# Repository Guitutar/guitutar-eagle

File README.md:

# Guitutar PCB Layout - Eagle Files

This repository is used for version control of PCB layout files for the creation of the Guitutar guitar teaching device. 

All PCB layouts within this repository were created by the Guitutar development team: Austin Peterson, Brian Rieder, Cole Giannotti, Jen Isaza

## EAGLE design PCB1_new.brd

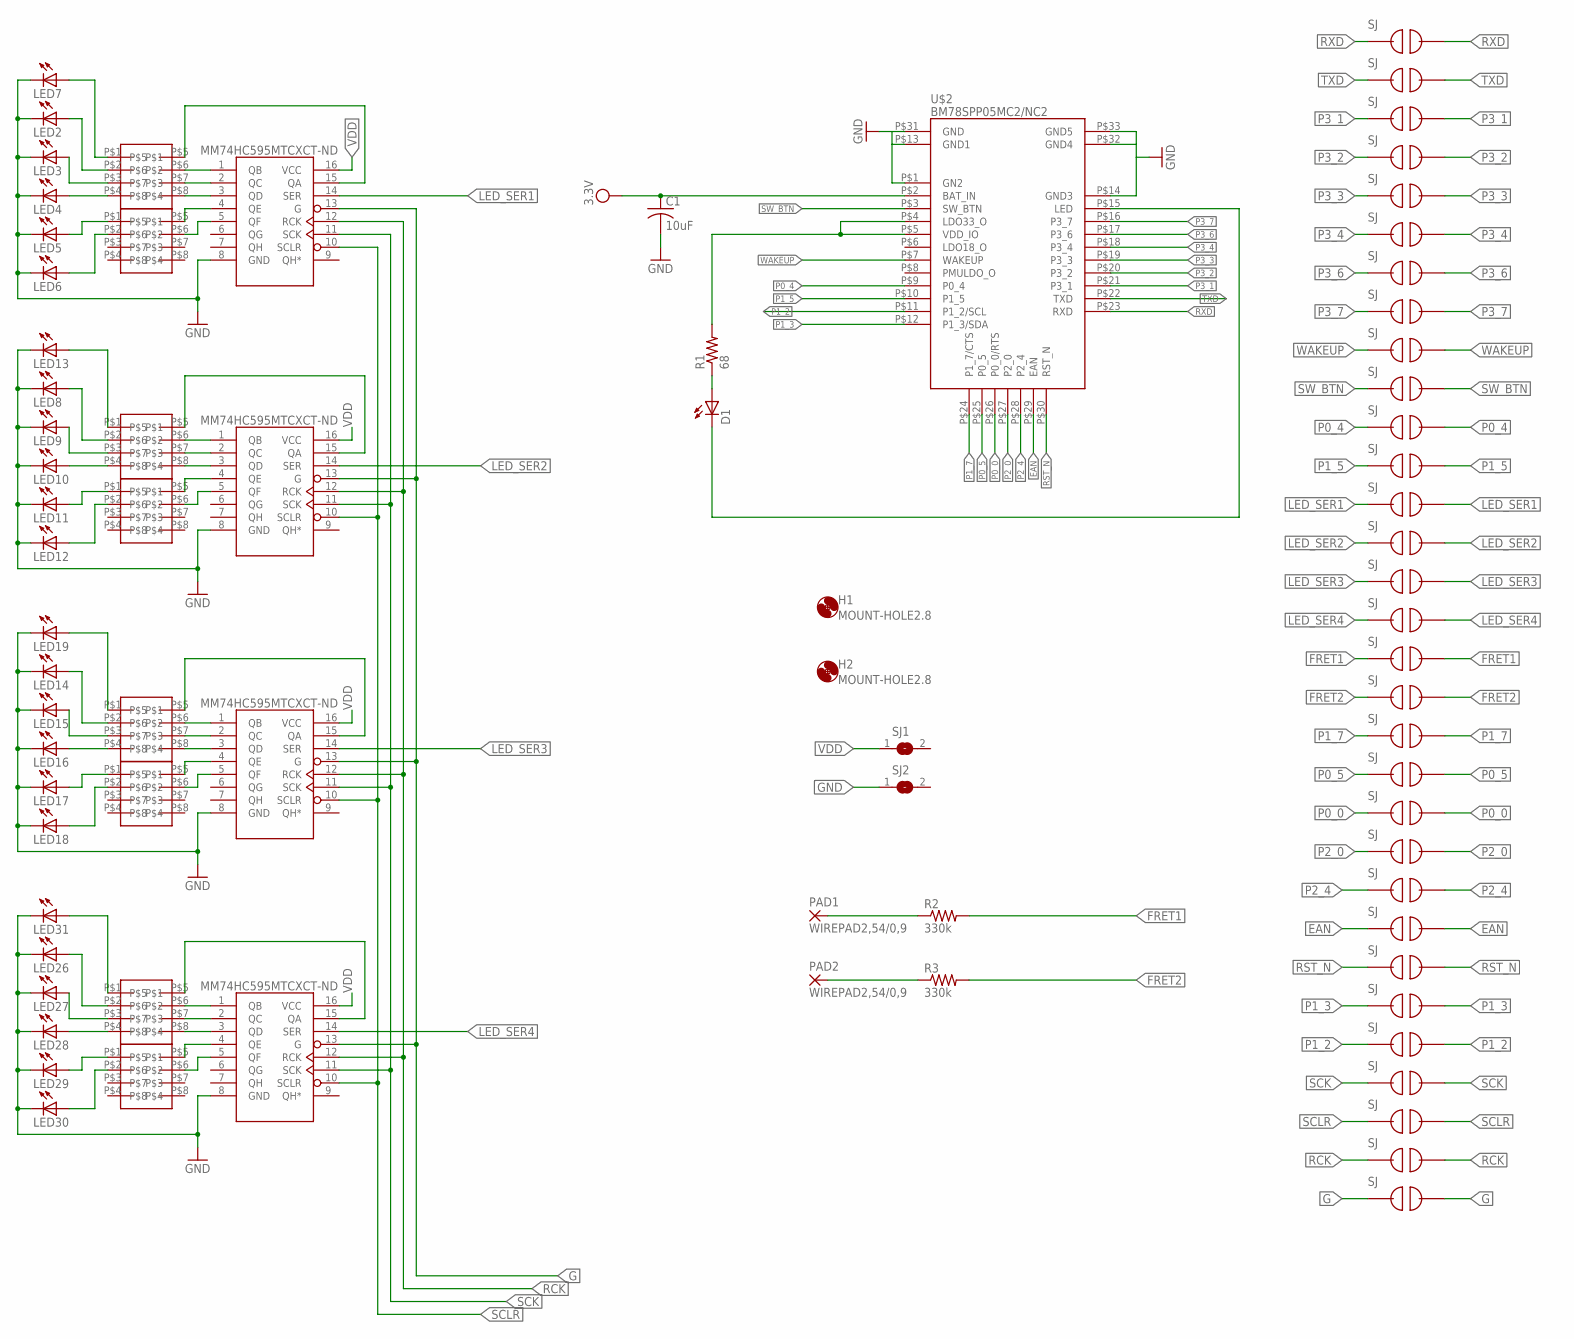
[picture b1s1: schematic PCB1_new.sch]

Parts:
C1: 10uF; C0805
D1: LEDSMT1206; 1206
H1, H2: MOUNT-HOLE2.8; 2,8
LED2, LED3, LED4, LED5, LED6, LED7, LED8, LED9, LED10, LED11, LED12, LED13, LED14, LED15, LED16, LED17, LED18, LED19, LED26, LED27, LED28, LED29, LED30, LED31: LEDSMT1206; 1206
PAD1, PAD2: WIREPAD2,54/0,9; 2,54/0,9
R1: 68; M0805
R2, R3: 330k; R0805
RN1, RN2: MNR04MRAPJ680; MNR04
SJ1, SJ2: SJW
U$1, U$3, U$4, U$5: MM74HC595TSSOP-LD16; MM74HC595MTCXCT-ND
U$2: BM78SPP05MC2/NC2
U$6, U$7, U$8, U$9, U$10, U$11, U$12, U$13, U$14, U$15, U$16, U$17, U$18, U$19, U$20, U$21, U$22, U$23, U$24, U$25, U$26, U$27, U$28, U$29, U$30, U$31, U$32, U$33, U$34, U$35, U$36: JUMPER
U$39, U$40, U$41, U$42, U$43, U$44: MNR04MRAPJ680; MNR04

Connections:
EAN: U$2.P$29 (EAN), U$26.P$1, U$26.P$2
FRET1: R2.2, U$19.P$1, U$19.P$2
FRET2: R3.2, U$20.P$1, U$20.P$2
G: U$1.13 (G), U$3.13 (G), U$4.13 (G), U$5.13 (G), U$30.P$1, U$30.P$2
GND: C1.2, LED2.C, LED3.C, LED4.C, LED5.C, LED6.C, LED7.C, LED8.C, LED9.C, LED10.C, LED11.C, LED12.C, LED13.C, LED14.C, LED15.C, LED16.C, LED17.C, LED18.C, LED19.C, LED26.C, LED27.C, LED28.C, LED29.C, LED30.C, LED31.C, SJ2.1, U$1.8 (GND), U$2.P$1 (GN2), U$2.P$13 (GND1), U$2.P$14 (GND3), U$2.P$31 (GND), U$2.P$32 (GND4), U$2.P$33 (GND5), U$3.8 (GND), U$4.8 (GND), U$5.8 (GND)
LED: D1.C, U$2.P$15 (LED)
LED_SER1: U$4.14 (SER), U$15.P$1, U$15.P$2
LED_SER2: U$1.14 (SER), U$16.P$1, U$16.P$2
LED_SER3: U$3.14 (SER), U$17.P$1, U$17.P$2
LED_SER4: U$5.14 (SER), U$18.P$1, U$18.P$2
unnamed: RN1.P$6, U$4.1 (QB)
unnamed: RN1.P$7, U$4.2 (QC)
unnamed: RN1.P$8, U$4.3 (QD)
unnamed: RN2.P$5, U$4.4 (QE)
unnamed: RN2.P$6, U$4.5 (QF)
unnamed: LED7.A, RN1.P$1
unnamed: RN1.P$5, U$4.15 (QA)
unnamed: LED2.A, RN1.P$2
unnamed: LED3.A, RN1.P$3
unnamed: LED4.A, RN1.P$4
unnamed: LED5.A, RN2.P$1
unnamed: LED6.A, RN2.P$2
unnamed: U$1.1 (QB), U$39.P$6
unnamed: U$1.2 (QC), U$39.P$7
unnamed: D1.A, R1.1
unnamed: R1.2, U$2.P$4 (LDO33_O), U$2.P$5 (VDD_IO)
unnamed: LED10.A, U$39.P$4
unnamed: LED16.A, U$41.P$4
unnamed: LED28.A, U$43.P$4
unnamed: U$1.3 (QD), U$39.P$8
unnamed: U$1.4 (QE), U$40.P$5
unnamed: U$1.5 (QF), U$40.P$6
unnamed: U$1.15 (QA), U$39.P$5
unnamed: LED13.A, U$39.P$1
unnamed: LED8.A, U$39.P$2
unnamed: LED9.A, U$39.P$3
unnamed: LED11.A, U$40.P$1
unnamed: LED12.A, U$40.P$2
unnamed: U$3.1 (QB), U$41.P$6
unnamed: U$3.2 (QC), U$41.P$7
unnamed: U$3.3 (QD), U$41.P$8
unnamed: U$3.4 (QE), U$42.P$5
unnamed: U$3.5 (QF), U$42.P$6
unnamed: U$3.15 (QA), U$41.P$5
unnamed: LED19.A, U$41.P$1
unnamed: LED14.A, U$41.P$2
unnamed: LED15.A, U$41.P$3
unnamed: LED17.A, U$42.P$1
unnamed: LED18.A, U$42.P$2
unnamed: U$5.1 (QB), U$43.P$6
unnamed: U$5.2 (QC), U$43.P$7
unnamed: U$5.3 (QD), U$43.P$8
unnamed: U$5.4 (QE), U$44.P$5
unnamed: U$5.5 (QF), U$44.P$6
unnamed: U$5.15 (QA), U$43.P$5
unnamed: LED31.A, U$43.P$1
unnamed: LED26.A, U$43.P$2
unnamed: LED27.A, U$43.P$3
unnamed: LED29.A, U$44.P$1
unnamed: LED30.A, U$44.P$2
unnamed: PAD1.1, R2.1
unnamed: PAD2.1, R3.1
P0_0: U$2.P$26 (P0_0/RTS), U$23.P$1, U$23.P$2
P0_4: U$2.P$9 (P0_4), U$13.P$1, U$13.P$2
P0_5: U$2.P$25 (P0_5), U$22.P$1, U$22.P$2
P1_2: U$2.P$11 (P1_2/SCL), U$29.P$1, U$29.P$2
P1_3: U$2.P$12 (P1_3/SDA), U$28.P$1, U$28.P$2
P1_5: U$2.P$10 (P1_5), U$14.P$1, U$14.P$2
P1_7: U$2.P$24 (P1_7/CTS), U$21.P$1, U$21.P$2
P2_0: U$2.P$27 (P2_0), U$24.P$1, U$24.P$2
P2_4: U$2.P$28 (P2_4), U$25.P$1, U$25.P$2
P3_1: U$2.P$21 (P3_1), U$33.P$1, U$33.P$2
P3_2: U$2.P$20 (P3_2), U$6.P$1, U$6.P$2
P3_3: U$2.P$19 (P3_3), U$7.P$1, U$7.P$2
P3_4: U$2.P$18 (P3_4), U$8.P$1, U$8.P$2
P3_6: U$2.P$17 (P3_6), U$9.P$1, U$9.P$2
P3_7: U$2.P$16 (P3_7), U$10.P$1, U$10.P$2
RCK: U$1.12 (RCK), U$3.12 (RCK), U$4.12 (RCK), U$5.12 (RCK), U$31.P$1, U$31.P$2
RST_N: U$2.P$30 (RST_N), U$27.P$1, U$27.P$2
RXD: U$2.P$23 (RXD), U$35.P$1, U$35.P$2
SCK: U$1.11 (SCK), U$3.11 (SCK), U$4.11 (SCK), U$5.11 (SCK), U$32.P$1, U$32.P$2
SCLR: U$1.10 (SCLR), U$3.10 (SCLR), U$4.10 (SCLR), U$5.10 (SCLR), U$36.P$1, U$36.P$2
SW_BTN: U$2.P$3 (SW_BTN), U$12.P$1, U$12.P$2
TXD: U$2.P$22 (TXD), U$34.P$1, U$34.P$2
VDD: C1.1, SJ1.1, U$1.16 (VCC), U$2.P$2 (BAT_IN), U$3.16 (VCC), U$4.16 (VCC), U$5.16 (VCC)
WAKEUP: U$2.P$7 (WAKEUP), U$11.P$1, U$11.P$2

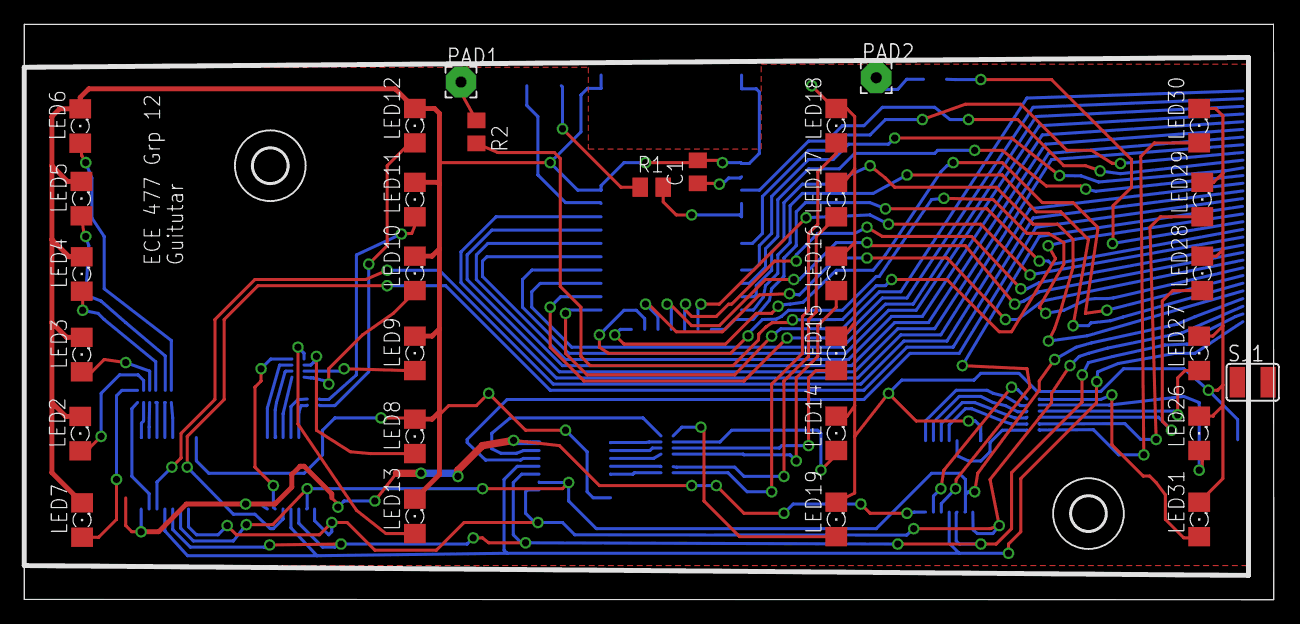
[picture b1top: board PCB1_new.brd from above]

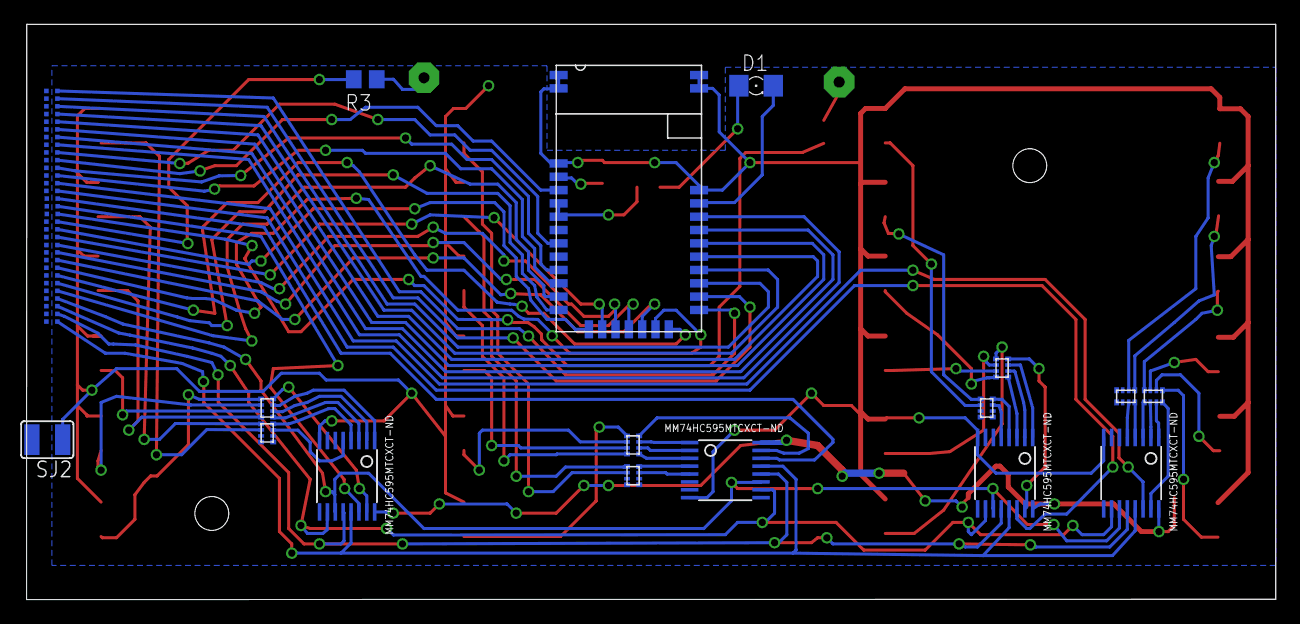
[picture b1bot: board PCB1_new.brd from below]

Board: 2 copper layers, 103.2 x 47.5 mm, 79 parts (47 on the bottom side), 86 nets.

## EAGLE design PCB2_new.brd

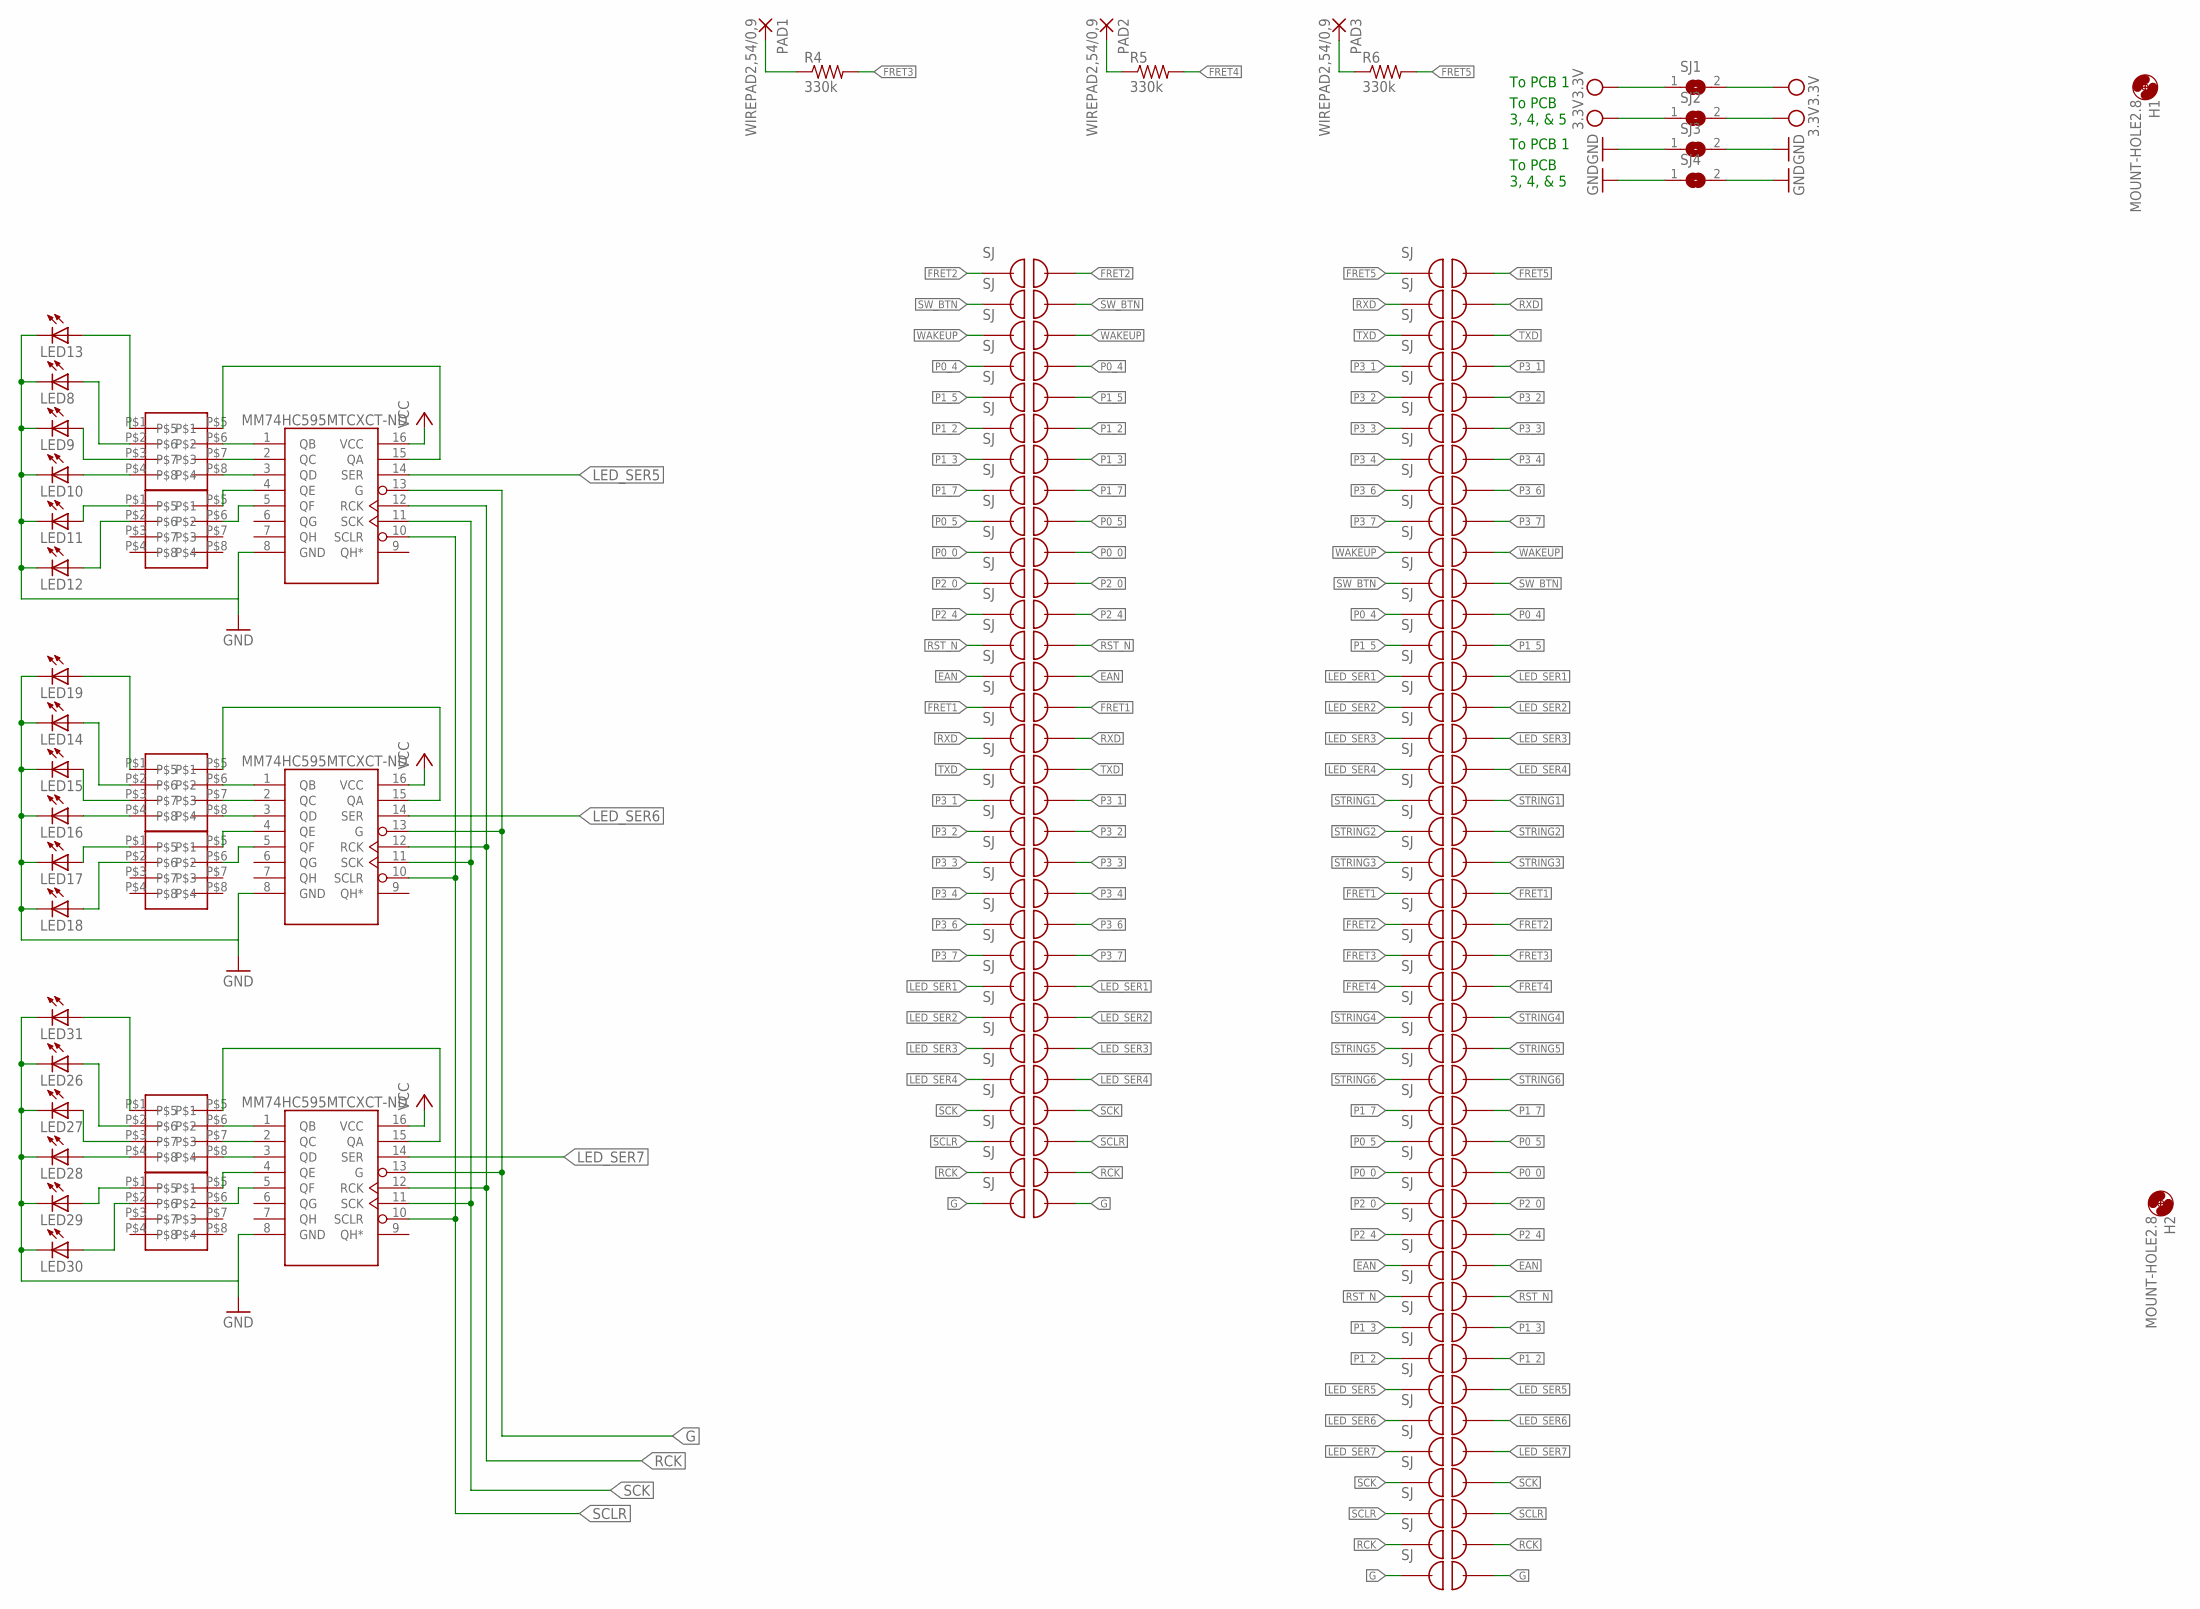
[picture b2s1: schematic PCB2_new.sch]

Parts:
H1, H2: MOUNT-HOLE2.8; 2,8
LED8, LED9, LED10, LED11, LED12, LED13, LED14, LED15, LED16, LED17, LED18, LED19, LED26, LED27, LED28, LED29, LED30, LED31: LEDSMT1206; 1206
PAD1, PAD2, PAD3: WIREPAD2,54/0,9; 2,54/0,9
R4, R5, R6: 330k; M0805
SJ1, SJ2, SJ3, SJ4: SJ
U$1, U$3, U$5: MM74HC595TSSOP-LD16; MM74HC595MTCXCT-ND
U$2, U$4, U$6, U$7, U$8, U$9, U$10, U$11, U$12, U$13, U$14, U$15, U$16, U$17, U$18, U$19, U$20, U$21, U$22, U$23, U$24, U$25, U$26, U$27, U$28, U$29, U$30, U$31, U$32, U$33, U$34, U$35, U$36, U$37, U$38, U$39, U$40, U$41, U$42, U$43, U$44, U$45, U$46, U$47, U$48, U$49, U$50, U$51, U$52, U$53, U$54, U$55, U$56, U$57, U$58, U$59, U$60, U$61, U$62, U$63, U$64, U$65, U$66, U$67, U$68, U$69, U$70, U$71, U$72, U$73, U$80, U$81, U$82, U$83: JUMPER
U$74, U$75, U$76, U$77, U$78, U$79: MNR04MRAPJ680; MNR04

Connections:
EAN: U$37.P$2, U$56.P$1, U$56.P$2
FRET1: U$25.P$2, U$57.P$1, U$57.P$2
FRET2: U$26.P$2, U$43.P$1, U$43.P$2
FRET3: PAD1.1, R4.1, R4.2, U$27.P$2
FRET4: PAD2.1, R5.1, R5.2, U$28.P$2
FRET5: R6.2, U$2.P$2
G: U$1.13 (G), U$3.13 (G), U$5.13 (G), U$73.P$1, U$73.P$2, U$83.P$1, U$83.P$2
GND: LED8.C, LED9.C, LED10.C, LED11.C, LED12.C, LED13.C, LED14.C, LED15.C, LED16.C, LED17.C, LED18.C, LED19.C, LED26.C, LED27.C, LED28.C, LED29.C, LED30.C, LED31.C, SJ3.1, SJ3.2, SJ4.1, SJ4.2, U$1.8 (GND), U$3.8 (GND), U$5.8 (GND)
LED_SER1: U$18.P$2, U$66.P$1, U$66.P$2
LED_SER2: U$19.P$2, U$67.P$1, U$67.P$2
LED_SER3: U$20.P$2, U$68.P$1, U$68.P$2
LED_SER4: U$21.P$2, U$69.P$1, U$69.P$2
LED_SER5: U$1.14 (SER), U$41.P$2
LED_SER6: U$3.14 (SER), U$42.P$2
LED_SER7: U$4.P$1, U$4.P$2, U$5.14 (SER)
unnamed: LED10.A, U$75.P$4
unnamed: LED12.A, U$74.P$2
unnamed: U$1.1 (QB), U$75.P$6
unnamed: U$1.2 (QC), U$75.P$7
unnamed: U$1.3 (QD), U$75.P$8
unnamed: U$1.4 (QE), U$74.P$5
unnamed: U$1.5 (QF), U$74.P$6
unnamed: LED16.A, U$76.P$4
unnamed: U$3.1 (QB), U$76.P$6
unnamed: U$3.2 (QC), U$76.P$7
unnamed: U$3.3 (QD), U$76.P$8
unnamed: U$3.4 (QE), U$77.P$5
unnamed: U$3.5 (QF), U$77.P$6
unnamed: LED17.A, U$77.P$1
unnamed: LED30.A, U$79.P$2
unnamed: LED28.A, U$78.P$4
unnamed: U$5.3 (QD), U$78.P$8
unnamed: U$5.2 (QC), U$78.P$7
unnamed: U$5.1 (QB), U$78.P$6
unnamed: U$5.4 (QE), U$79.P$5
unnamed: U$5.5 (QF), U$79.P$6
unnamed: U$1.15 (QA), U$75.P$5
unnamed: LED13.A, U$75.P$1
unnamed: LED8.A, U$75.P$2
unnamed: LED9.A, U$75.P$3
unnamed: LED11.A, U$74.P$1
unnamed: PAD3.1, R6.1
unnamed: U$3.15 (QA), U$76.P$5
unnamed: LED19.A, U$76.P$1
unnamed: LED14.A, U$76.P$2
unnamed: LED15.A, U$76.P$3
unnamed: LED18.A, U$77.P$2
unnamed: U$5.15 (QA), U$78.P$5
unnamed: LED31.A, U$78.P$1
unnamed: LED26.A, U$78.P$2
unnamed: LED27.A, U$78.P$3
unnamed: LED29.A, U$79.P$1
P0_0: U$34.P$2, U$52.P$1, U$52.P$2
P0_4: U$16.P$2, U$46.P$1, U$46.P$2
P0_5: U$33.P$2, U$51.P$1, U$51.P$2
P1_2: U$40.P$2, U$48.P$1, U$48.P$2
P1_3: U$39.P$2, U$49.P$1, U$49.P$2
P1_5: U$17.P$2, U$47.P$1, U$47.P$2
P1_7: U$32.P$2, U$50.P$1, U$50.P$2
P2_0: U$35.P$2, U$53.P$1, U$53.P$2
P2_4: U$36.P$2, U$54.P$1, U$54.P$2
P3_1: U$8.P$2, U$60.P$1, U$60.P$2
P3_2: U$9.P$2, U$61.P$1, U$61.P$2
P3_3: U$10.P$2, U$62.P$1, U$62.P$2
P3_4: U$11.P$2, U$63.P$1, U$63.P$2
P3_6: U$12.P$2, U$64.P$1, U$64.P$2
P3_7: U$13.P$2, U$65.P$1, U$65.P$2
RCK: U$1.12 (RCK), U$3.12 (RCK), U$5.12 (RCK), U$72.P$1, U$72.P$2, U$82.P$1, U$82.P$2
RST_N: U$38.P$2, U$55.P$1, U$55.P$2
RXD: U$6.P$2, U$58.P$1, U$58.P$2
SCK: U$1.11 (SCK), U$3.11 (SCK), U$5.11 (SCK), U$70.P$1, U$70.P$2, U$80.P$1, U$80.P$2
SCLR: U$1.10 (SCLR), U$3.10 (SCLR), U$5.10 (SCLR), U$71.P$1, U$71.P$2, U$81.P$1, U$81.P$2
STRING1: U$22.P$2
STRING2: U$23.P$2
STRING3: U$24.P$2
STRING4: U$29.P$2
STRING5: U$30.P$2
STRING6: U$31.P$2
SW_BTN: U$15.P$2, U$44.P$1, U$44.P$2
TXD: U$7.P$2, U$59.P$1, U$59.P$2
VCC: U$1.16 (VCC), U$3.16 (VCC), U$5.16 (VCC)
VDD: SJ1.1, SJ1.2, SJ2.1, SJ2.2
WAKEUP: U$14.P$2, U$45.P$1, U$45.P$2

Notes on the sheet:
To PCB 1
To PCB 3, 4, & 5

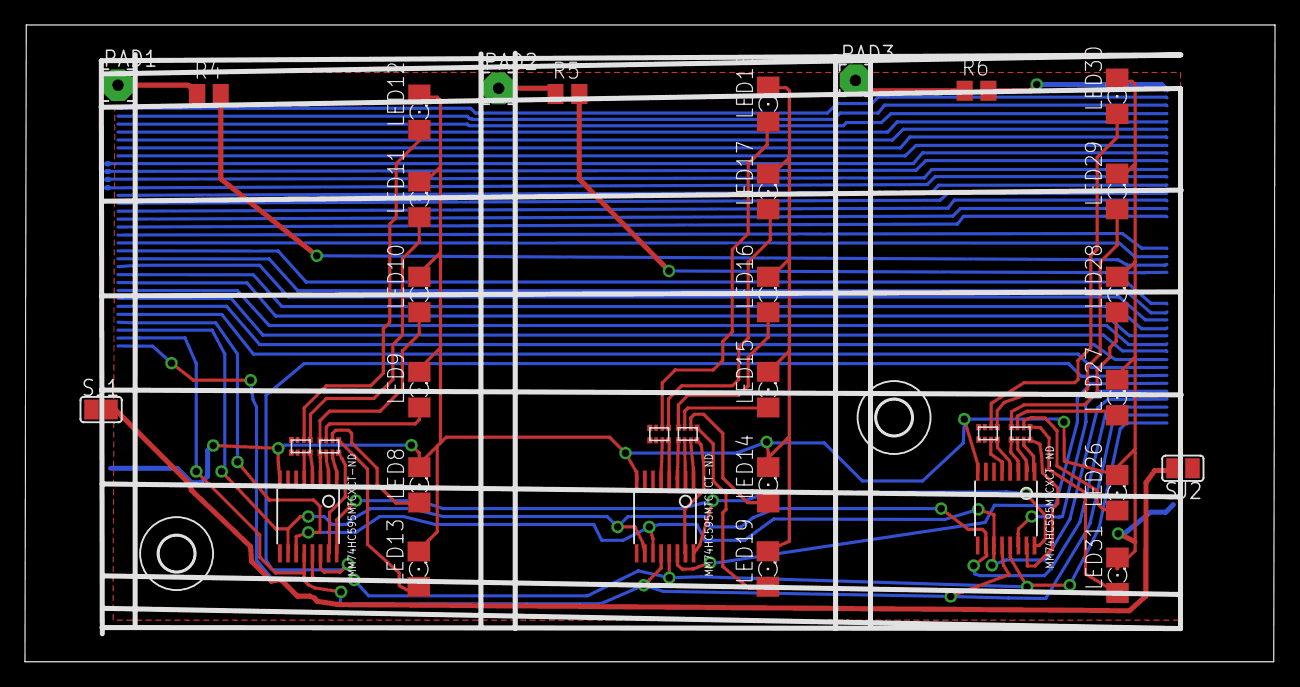
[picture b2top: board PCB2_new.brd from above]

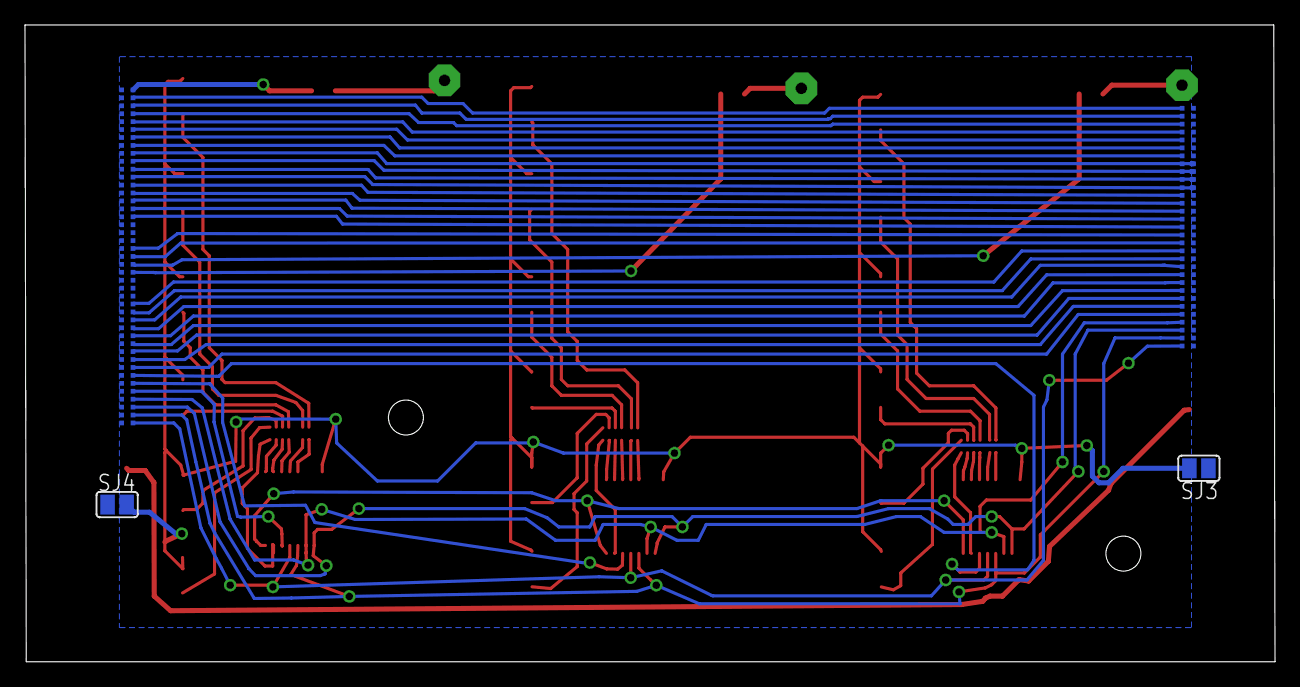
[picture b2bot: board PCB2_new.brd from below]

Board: 2 copper layers, 100.1 x 51.0 mm, 113 parts (76 on the bottom side), 77 nets.

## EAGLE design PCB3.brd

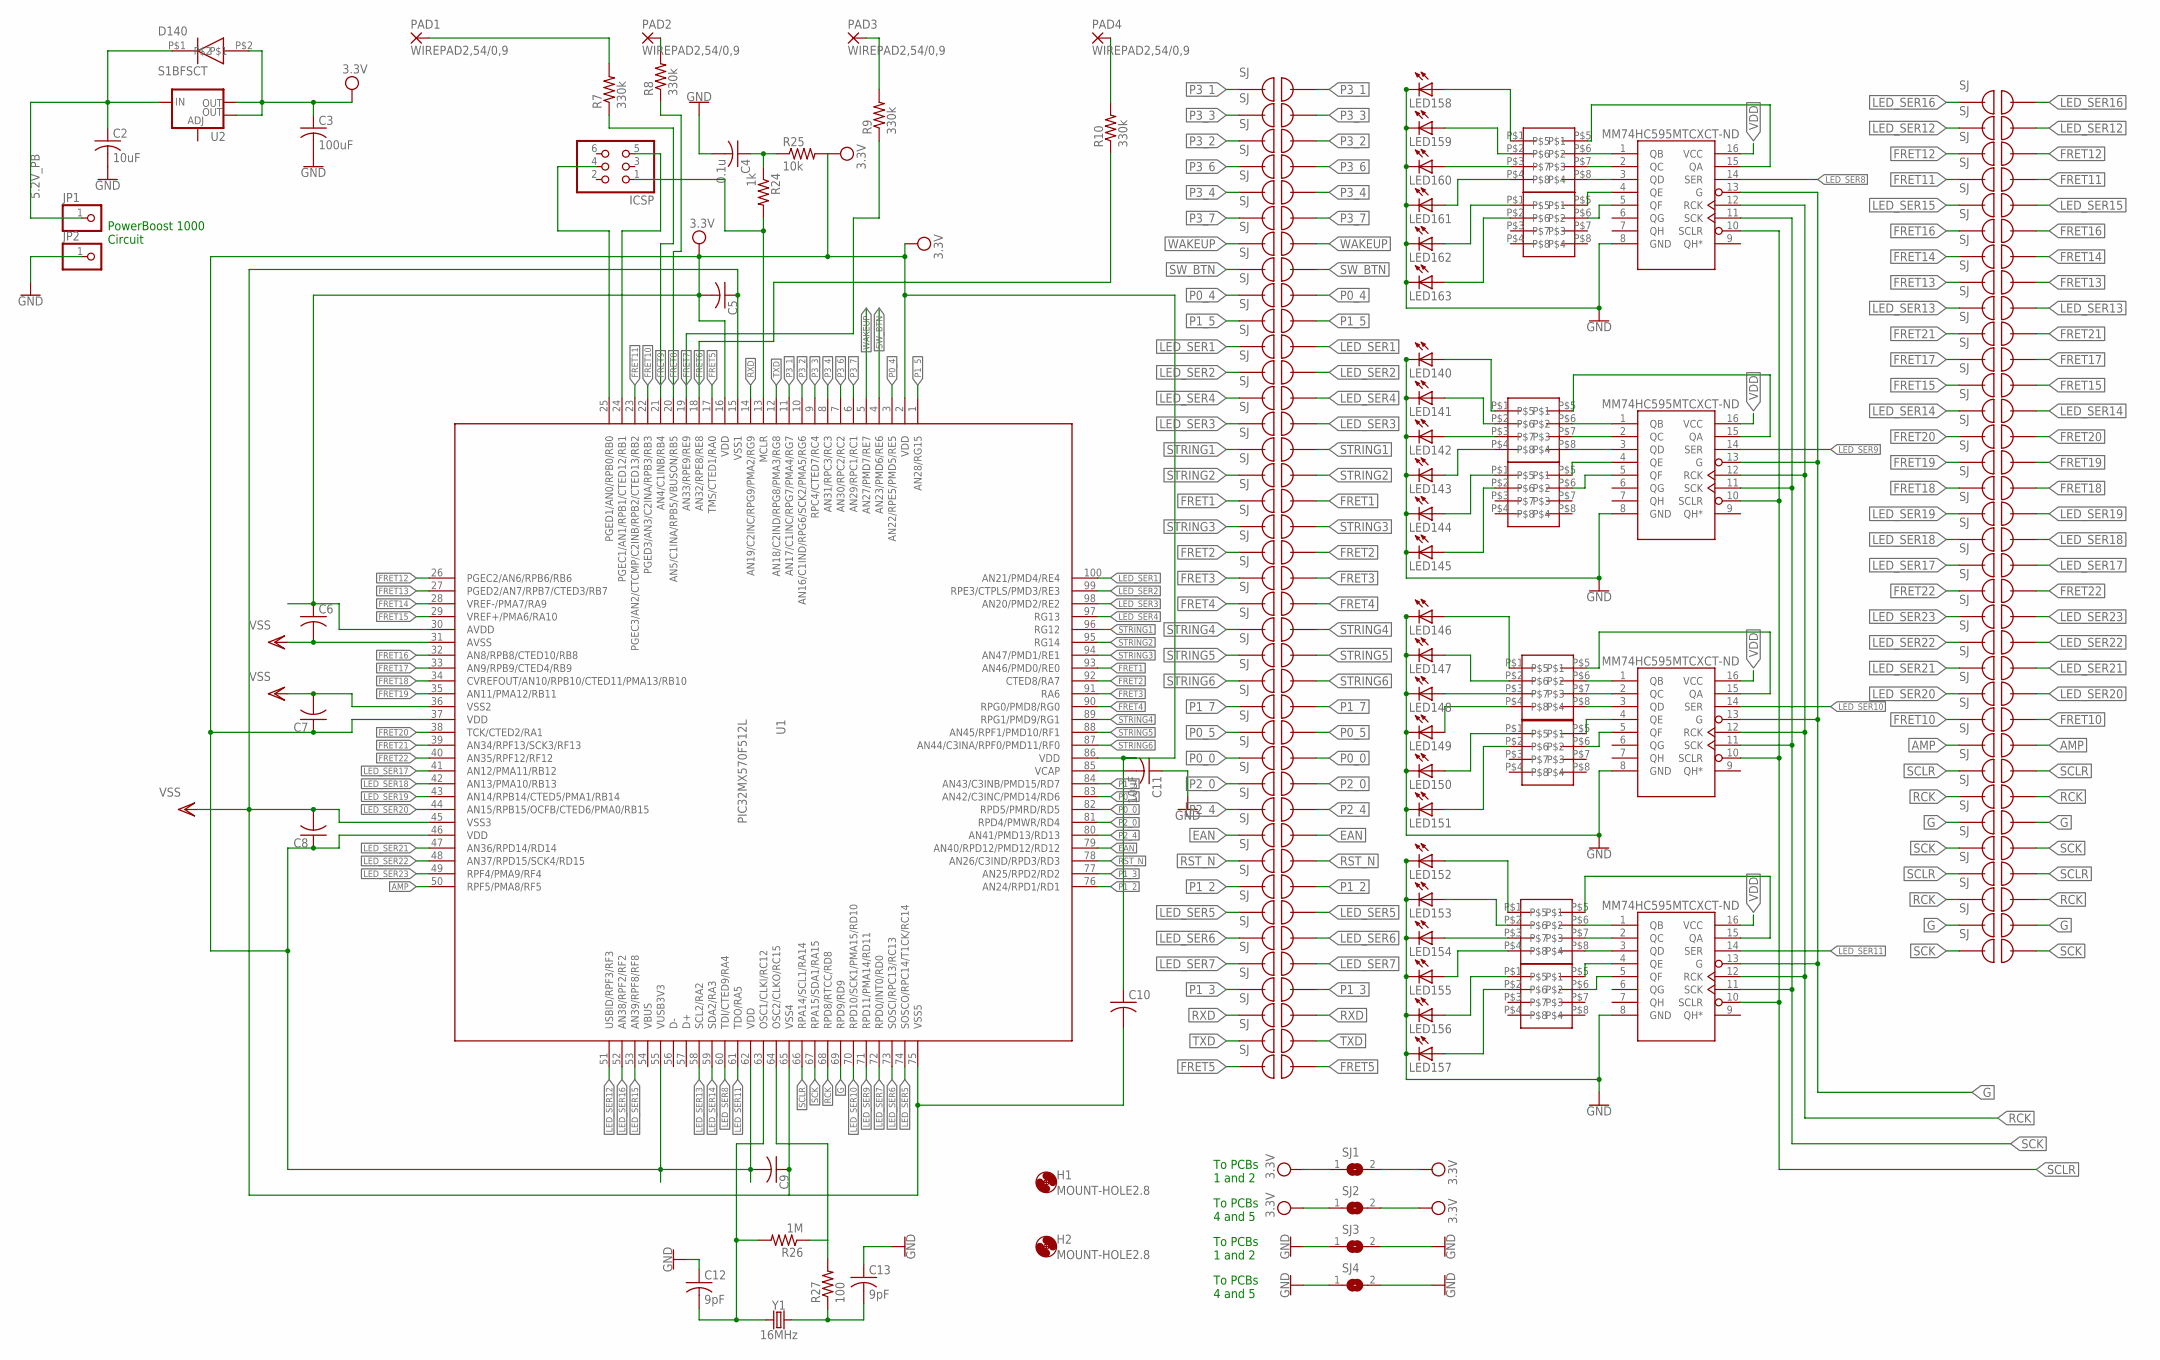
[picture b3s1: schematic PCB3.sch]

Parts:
C2, C11: 10uF; C0805
C3: 100uF; C0805
C4: 0.1u; C0805
C5, C6, C7, C8, C9, C10: C-USC0805; C0805
C12, C13: 9pF; C0805
D140: S1BFSCT
H1, H2: MOUNT-HOLE2.8; 2,8
ICSP: PINHD-2X3; 2X03
JP1, JP2: PINHD-1X1; 1X01
LED140, LED141, LED142, LED143, LED144, LED145, LED146, LED147, LED148, LED149, LED150, LED151, LED152, LED153, LED154, LED155, LED156, LED157, LED158, LED159, LED160, LED161, LED162, LED163: LEDSMT1206; 1206
PAD1, PAD2, PAD3, PAD4: WIREPAD2,54/0,9; 2,54/0,9
R7, R8, R9, R10: 330k; M0805
R24: 1k; M0805
R25: 10k; M0805
R26: 1M; M0805
R27: 100; M0805
RXD: JUMPER
SJ1, SJ2, SJ3, SJ4: SJW
U1: PIC32MX570F512L; TQFP100-14X14
U2: V_REG_LM1117SOT223; SOT223
U$1, U$2, U$3, U$4, U$5, U$6, U$7, U$8, U$9, U$10, U$11, U$12, U$13, U$14, U$15, U$16, U$17, U$18, U$19, U$20, U$21, U$22, U$23, U$24, U$25, U$30, U$31, U$32, U$33, U$34, U$35, U$36, U$37, U$38, U$39, U$40, U$41, U$42, U$43, U$44, U$45, U$46, U$47, U$48, U$49, U$50, U$51, U$52, U$53, U$54, U$55, U$56, U$57, U$58, U$59, U$60, U$61, U$62, U$63, U$64, U$65, U$66, U$67, U$68, U$69, U$70, U$79, U$80, U$81, U$82, U$83, U$84: JUMPER
U$26, U$27, U$28, U$29: MM74HC595TSSOP-LD16; MM74HC595MTCXCT-ND
U$71, U$72, U$73, U$74, U$75, U$76, U$77, U$78: MNR04MRAPJ680; MNR04
Y1: 16MHz; CRYSTAL-SMD-5X3.2-2PAD

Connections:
5.2V_PB: C2.1, D140.P$1, JP1.1, U2.3 (IN)
AMP: U1.50 (RPF5/PMA8/RF5), U$70.P$2
EAN: U1.79 (AN40/RPD12/PMD12/RD12), U$35.P$2
FRET1: U1.93 (AN46/PMD0/RE0), U$18.P$2
FRET2: U1.92 (CTED8/RA7), U$20.P$2
FRET3: U1.91 (RA6), U$21.P$2
FRET4: U1.90 (RPG0/PMD8/RG0), U$22.P$2
FRET5: U1.17 (TMS/CTED1/RA0), U$43.P$1, U$43.P$2
FRET6: R10.1, U1.18 (AN32/RPE8/RE8)
FRET7: R9.1, U1.19 (AN33/RPE9/RE9)
FRET8: R8.1, U1.20 (AN5/C1INA/RPB5/VBUSON/RB5)
FRET9: R7.1, U1.21 (AN4/C1INB/RB4)
FRET10: U1.22 (PGED3/AN3/C2INA/RPB3/RB3), U$69.P$2
FRET11: U1.23 (PGEC3/AN2/CTCMP/C2INB/RPB2/CTED13/RB2), U$48.P$2
FRET12: U1.26 (PGEC2/AN6/RPB6/RB6), U$47.P$2
FRET13: U1.27 (PGED2/AN7/RPB7/CTED3/RB7), U$52.P$2
FRET14: U1.28 (VREF-/PMA7/RA9), U$51.P$2
FRET15: U1.29 (VREF+/PMA6/RA10), U$56.P$2
FRET16: U1.32 (AN8/RPB8/CTED10/RB8), U$50.P$2
FRET17: U1.33 (AN9/RPB9/CTED4/RB9), U$55.P$2
FRET18: U1.34 (CVREFOUT/AN10/RPB10/CTED11/PMA13/RB10), U$60.P$2
FRET19: U1.35 (AN11/PMA12/RB11), U$59.P$2
FRET20: U1.38 (TCK/CTED2/RA1), U$58.P$2
FRET21: U1.39 (AN34/RPF13/SCK3/RF13), U$54.P$2
FRET22: U1.40 (AN35/RPF12/RF12), U$64.P$2
G: U1.69 (RPD9/RD9), U$26.13 (G), U$27.13 (G), U$28.13 (G), U$29.13 (G), U$80.P$2, U$84.P$2
GND: C2.2, C3.2, C4.2, C11.1, C12.1, C13.1, JP2.1, LED140.C, LED141.C, LED142.C, LED143.C, LED144.C, LED145.C, LED146.C, LED147.C, LED148.C, LED149.C, LED150.C, LED151.C, LED152.C, LED153.C, LED154.C, LED155.C, LED156.C, LED157.C, LED158.C, LED159.C, LED160.C, LED161.C, LED162.C, LED163.C, SJ3.1, SJ3.2, SJ4.1, SJ4.2, U$26.8 (GND), U$27.8 (GND), U$28.8 (GND), U$29.8 (GND)
LED_SER1: U1.100 (AN21/PMD4/RE4), U$12.P$2
LED_SER2: U1.99 (RPE3/CTPLS/PMD3/RE3), U$13.P$2
LED_SER3: U1.98 (AN20/PMD2/RE2), U$15.P$2
LED_SER4: U1.97 (RG13), U$14.P$2
LED_SER5: U1.74 (SOSCO/RPC14/T1CK/RC14), U$38.P$2
LED_SER6: U1.73 (SOSCI/RPC13/RC13), U$39.P$2
LED_SER7: U1.72 (RPD0/INT0/RD0), U$40.P$2
LED_SER8: U1.60 (TDI/CTED9/RA4), U$26.14 (SER)
LED_SER9: U1.71 (RPD11/PMA14/RD11), U$27.14 (SER)
LED_SER10: U1.70 (RPD10/SCK1/PMA15/RD10), U$28.14 (SER)
LED_SER11: U1.61 (TDO/RA5), U$29.14 (SER)
LED_SER12: U1.51 (USBID/RPF3/RF3), U$46.P$2
LED_SER13: U1.58 (SCL2/RA2), U$53.P$2
LED_SER14: U1.59 (SDA2/RA3), U$57.P$2
LED_SER15: U1.53 (AN39/RPF8/RF8), U$49.P$2
LED_SER16: U1.52 (AN38/RPF2/RF2), U$45.P$2
LED_SER17: U1.41 (AN12/PMA11/RB12), U$63.P$2
LED_SER18: U1.42 (AN13/PMA10/RB13), U$62.P$2
LED_SER19: U1.43 (AN14/RPB14/CTED5/PMA1/RB14), U$61.P$2
LED_SER20: U1.44 (AN15/RPB15/OCFB/CTED6/PMA0/RB15), U$68.P$2
LED_SER21: U1.47 (AN36/RPD14/RD14), U$67.P$2
LED_SER22: U1.48 (AN37/RPD15/SCK4/RD15), U$66.P$2
LED_SER23: U1.49 (RPF4/PMA9/RF4), U$65.P$2
unnamed: C4.1, R24.1, R25.1
unnamed: ICSP.5, U1.24 (PGEC1/AN1/RPB1/CTED12/RB1)
unnamed: PAD1.1, R7.2
unnamed: PAD2.1, R8.2
unnamed: PAD3.1, R9.2
unnamed: U$28.5 (QF), U$76.P$6
unnamed: PAD4.1, R10.2
unnamed: LED146.A, U$75.P$1
unnamed: LED147.A, U$75.P$2
unnamed: LED148.A, U$75.P$3
unnamed: C11.2, U1.85 (VCAP)
unnamed: ICSP.1, R24.2, U1.13 (MCLR)
unnamed: ICSP.4, U1.25 (PGED1/AN0/RPB0/RB0)
unnamed: LED149.A, U$75.P$4
unnamed: LED150.A, U$76.P$1
unnamed: LED151.A, U$76.P$2
unnamed: U$27.1 (QB), U$73.P$6
unnamed: U$27.2 (QC), U$73.P$7
unnamed: U$27.3 (QD), U$73.P$8
unnamed: U$27.4 (QE), U$74.P$5
unnamed: U$27.5 (QF), U$74.P$6
unnamed: LED142.A, U$73.P$3
unnamed: U$26.1 (QB), U$71.P$6
unnamed: U$26.2 (QC), U$71.P$7
unnamed: U$26.3 (QD), U$71.P$8
unnamed: U$26.4 (QE), U$72.P$5
unnamed: U$26.5 (QF), U$72.P$6
unnamed: U$27.15 (QA), U$73.P$5
unnamed: LED140.A, U$73.P$1
unnamed: LED141.A, U$73.P$2
unnamed: LED160.A, U$71.P$3
unnamed: LED143.A, U$73.P$4
unnamed: U$29.1 (QB), U$77.P$6
unnamed: C13.2, R27.1, Y1.P$2 (2)
unnamed: C12.2, R26.2, U1.63 (OSC1/CLKI/RC12), Y1.P$1 (1)
unnamed: U$29.2 (QC), U$77.P$7
unnamed: U$29.3 (QD), U$77.P$8
unnamed: U$29.4 (QE), U$78.P$5
unnamed: U$29.5 (QF), U$78.P$6
unnamed: LED153.A, U$77.P$2
unnamed: LED154.A, U$77.P$3
unnamed: LED155.A, U$77.P$4
unnamed: LED144.A, U$74.P$1
unnamed: LED145.A, U$74.P$2
unnamed: U$28.1 (QB), U$75.P$6
unnamed: U$28.2 (QC), U$75.P$7
unnamed: U$28.3 (QD), U$75.P$8
unnamed: U$28.4 (QE), U$76.P$5
unnamed: U$28.15 (QA), U$75.P$5
unnamed: U$29.15 (QA), U$77.P$5
unnamed: LED152.A, U$77.P$1
unnamed: LED156.A, U$78.P$1
unnamed: LED157.A, U$78.P$2
unnamed: U$26.15 (QA), U$71.P$5
unnamed: LED158.A, U$71.P$1
unnamed: LED161.A, U$71.P$4
unnamed: LED162.A, U$72.P$1
unnamed: LED163.A, U$72.P$2
unnamed: LED159.A, U$71.P$2
OSC2: R26.1, R27.2, U1.64 (OSC2/CLKO/RC15)
P0_0: U1.82 (RPD5/PMRD/RD5), U$32.P$2
P0_4: U1.3 (AN22/RPE5/PMD5/RE5), U$10.P$2
P0_5: U1.83 (AN42/C3INC/PMD14/RD6), U$31.P$2
P1_2: U1.76 (AN24/RPD1/RD1), U$37.P$2
P1_3: U1.77 (AN25/RPD2/RD2), U$41.P$2
P1_5: U1.1 (AN28/RG15), U$11.P$2
P1_7: U1.84 (AN43/C3INB/PMD15/RD7), U$30.P$2
P2_0: U1.81 (RPD4/PMWR/RD4), U$33.P$2
P2_4: U1.80 (AN41/PMD13/RD13), U$34.P$2
P3_1: U1.11 (AN17/C1INC/RPG7/PMA4/RG7), U$1.P$2
P3_2: U1.10 (AN16/C1IND/RPG6/SCK2/PMA5/RG6), U$4.P$2
P3_3: U1.9 (RPC4/CTED7/RC4), U$3.P$2
P3_4: U1.8 (AN31/RPC3/RC3), U$6.P$2
P3_6: U1.7 (AN30/RPC2/RC2), U$5.P$2
P3_7: U1.6 (AN29/RPC1/RC1), U$7.P$2
RCK: U1.68 (RPD8/RTCC/RD8), U$26.12 (RCK), U$27.12 (RCK), U$28.12 (RCK), U$29.12 (RCK), U$79.P$2, U$83.P$2
RST_N: U1.78 (AN26/C3IND/RPD3/RD3), U$36.P$2
RXD: RXD.P$1, RXD.P$2, U1.14 (AN19/C2INC/RPG9/PMA2/RG9)
SCK: U1.67 (RPA15/SDA1/RA15), U$26.11 (SCK), U$27.11 (SCK), U$28.11 (SCK), U$29.11 (SCK), U$42.P$1, U$42.P$2, U$81.P$1, U$81.P$2
SCLR: U1.66 (RPA14/SCL1/RA14), U$2.P$2, U$26.10 (SCLR), U$27.10 (SCLR), U$28.10 (SCLR), U$29.10 (SCLR), U$82.P$2
STRING1: U1.96 (RG12), U$16.P$2
STRING2: U1.95 (RG14), U$17.P$2
STRING3: U1.94 (AN47/PMD1/RE1), U$19.P$2
STRING4: U1.89 (RPG1/PMD9/RG1), U$23.P$2
STRING5: U1.88 (AN45/RPF1/PMD10/RF1), U$24.P$2
STRING6: U1.87 (AN44/C3INA/RPF0/PMD11/RF0), U$25.P$2
SW_BTN: U1.4 (AN23/PMD6/RE6), U$9.P$2
TXD: U1.12 (AN18/C2IND/RPG8/PMA3/RG8), U$44.P$1, U$44.P$2
VDD: C3.1, C5.2, C6.1, C7.1, C8.1, C9.2, C10.1, D140.P$2, R25.2, SJ1.1, SJ1.2, SJ2.1, SJ2.2, U1.2 (VDD), U1.16 (VDD), U1.30 (AVDD), U1.37 (VDD), U1.46 (VDD), U1.55 (VUSB3V3), U1.62 (VDD), U1.86 (VDD), U2.2 (OUT), U2.4 (OUT), U$26.16 (VCC), U$27.16 (VCC), U$28.16 (VCC), U$29.16 (VCC)
VSS: C5.1, C6.2, C7.2, C8.2, C9.1, C10.2, U1.15 (VSS1), U1.31 (AVSS), U1.36 (VSS2), U1.45 (VSS3), U1.65 (VSS4), U1.75 (VSS5)
WAKEUP: U1.5 (AN27/PMD7/RE7), U$8.P$2

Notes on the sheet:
PowerBoost 1000 Circuit
To PCBs 1 and 2
To PCBs 4 and 5

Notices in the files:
parts and their libraries:
SparkFun-Clocks: Licensing: Creative Commons ShareAlike 4.0 International - https://creativecommons.org/licenses/by-sa/4.0
